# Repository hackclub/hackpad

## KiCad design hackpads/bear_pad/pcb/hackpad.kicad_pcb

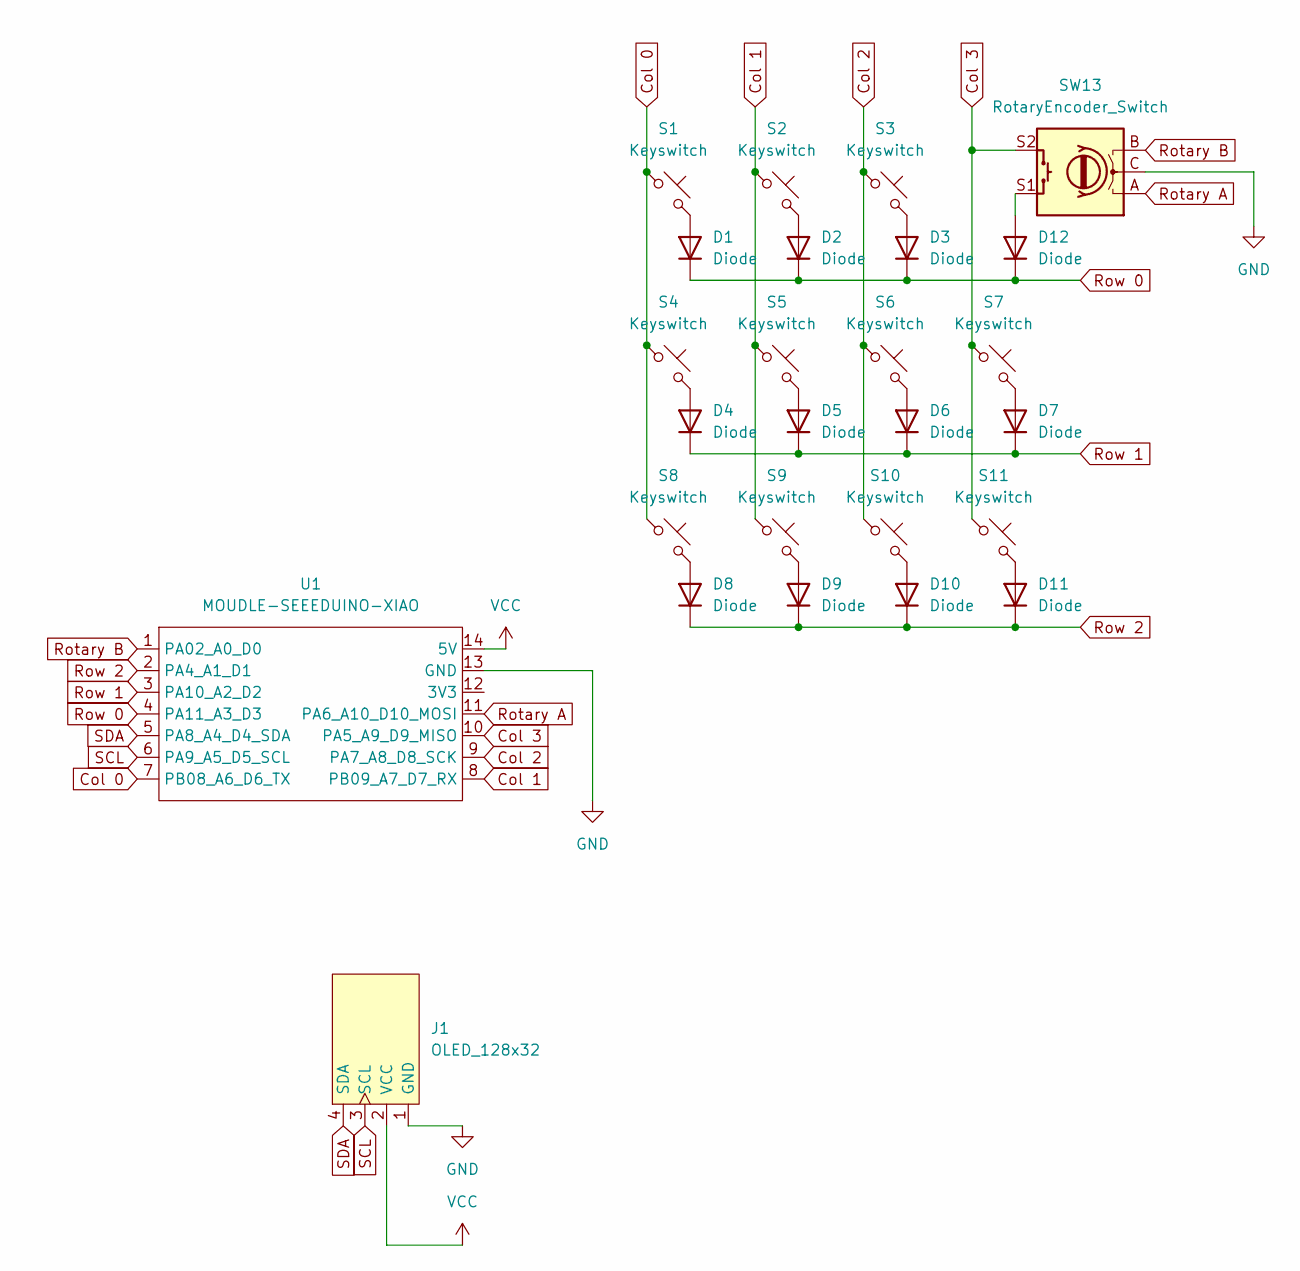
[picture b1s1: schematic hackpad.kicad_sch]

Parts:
D1, D2, D3, D4, D5, D6, D7, D8, D9, D10, D11, D12: Diode; Diode_DO-35
J1: OLED_128x32
S1, S2, S3, S4, S5, S6, S7, S8, S9, S10, S11: Keyswitch; MX_PCB_1.00u
SW13: RotaryEncoder_Switch; RotaryEncoder_Alps_EC11E-Switch_Vertical_H20mm
U1: MOUDLE-SEEEDUINO-XIAO; XIAO-Generic-Hybrid-14P-2.54-21X17.8MM

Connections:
Col 0: S1.1, S4.1, S8.1, U1.7 (PB08_A6_D6_TX)
Col 1: S2.1, S5.1, S9.1, U1.8 (PB09_A7_D7_RX)
Col 2: S3.1, S6.1, S10.1, U1.9 (PA7_A8_D8_SCK)
Col 3: S7.1, S11.1, SW13.S2, U1.10 (PA5_A9_D9_MISO)
GND: J1.1 (GND), SW13.C, U1.13 (GND)
unnamed: D1.2 (A), S1.2
unnamed: D2.2 (A), S2.2
unnamed: D3.2 (A), S3.2
unnamed: D4.2 (A), S4.2
unnamed: D5.2 (A), S5.2
unnamed: D6.2 (A), S6.2
unnamed: D7.2 (A), S7.2
unnamed: D8.2 (A), S8.2
unnamed: D9.2 (A), S9.2
unnamed: D10.2 (A), S10.2
unnamed: D11.2 (A), S11.2
unnamed: D12.2 (A), SW13.S1
Rotary A: SW13.A, U1.11 (PA6_A10_D10_MOSI)
Rotary B: SW13.B, U1.1 (PA02_A0_D0)
Row 0: D1.1 (K), D2.1 (K), D3.1 (K), D12.1 (K), U1.4 (PA11_A3_D3)
Row 1: D4.1 (K), D5.1 (K), D6.1 (K), D7.1 (K), U1.3 (PA10_A2_D2)
Row 2: D8.1 (K), D9.1 (K), D10.1 (K), D11.1 (K), U1.2 (PA4_A1_D1)
SCL: J1.3 (SCL), U1.6 (PA9_A5_D5_SCL)
SDA: J1.4 (SDA), U1.5 (PA8_A4_D4_SDA)
VCC: J1.2 (VCC), U1.14 (5V)

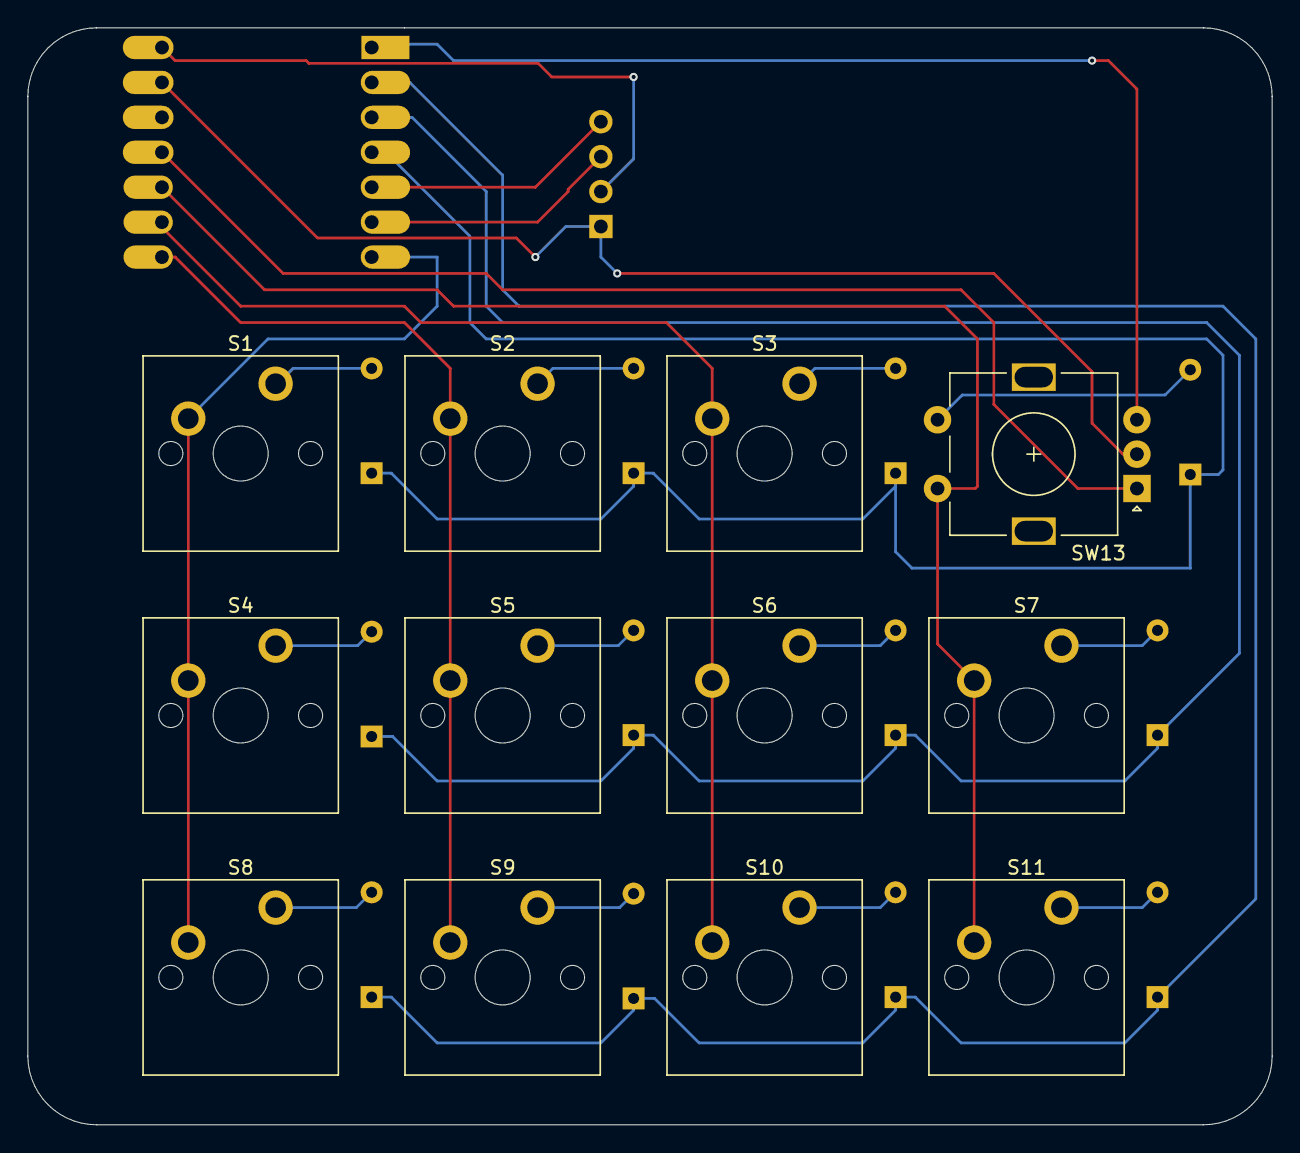
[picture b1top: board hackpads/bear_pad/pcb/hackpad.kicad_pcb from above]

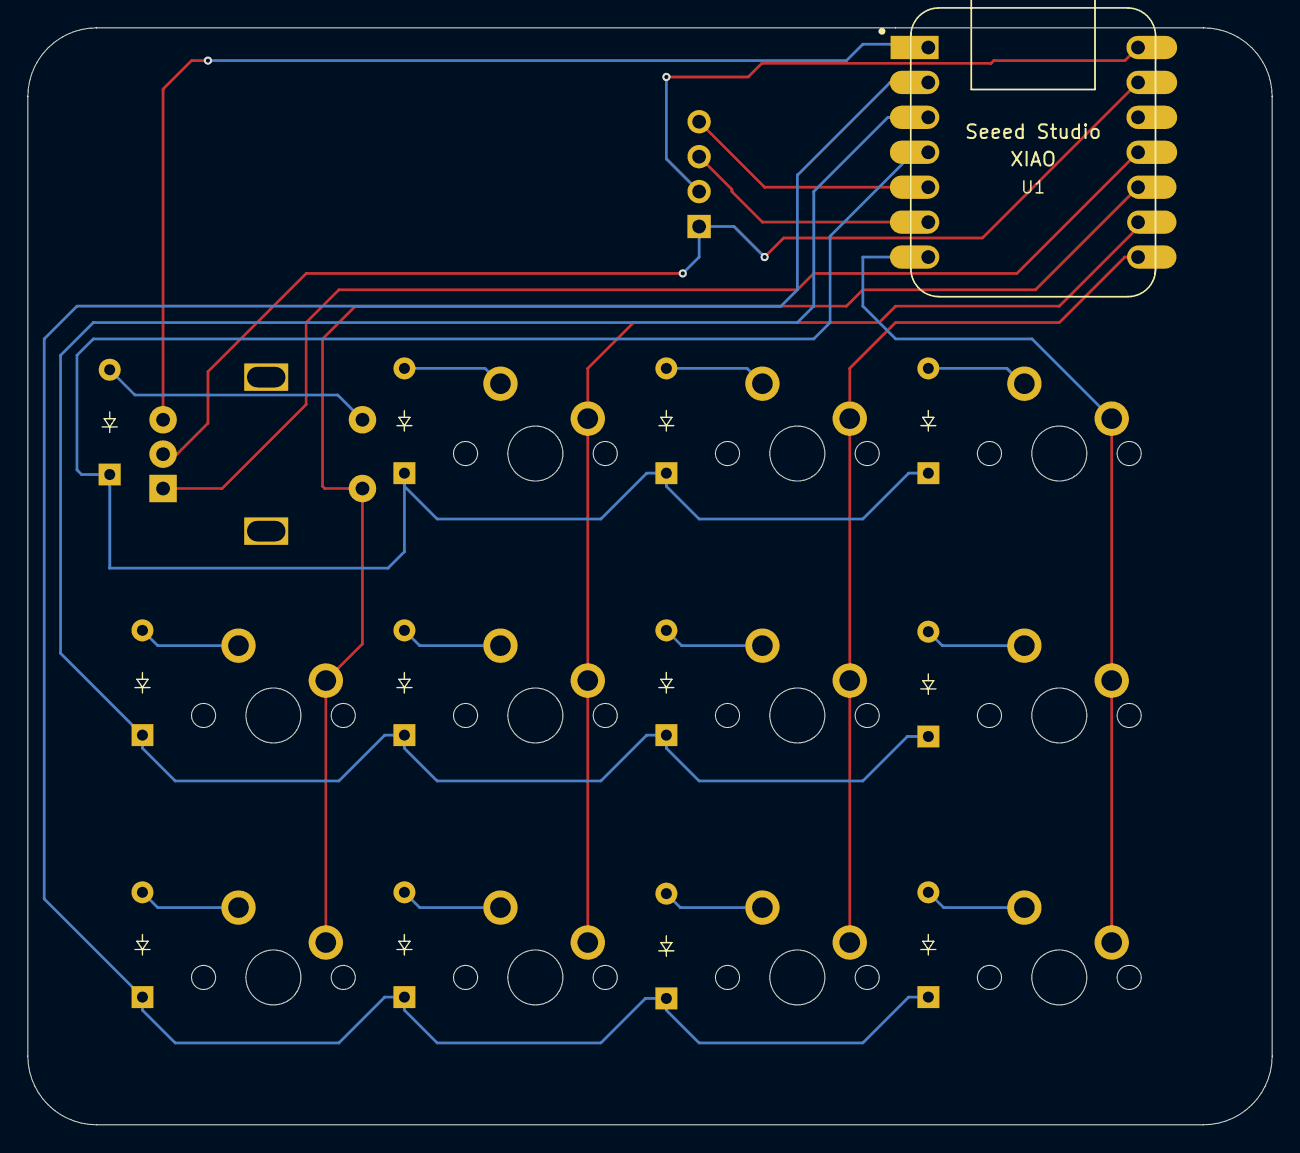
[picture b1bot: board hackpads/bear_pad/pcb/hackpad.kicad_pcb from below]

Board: 2 copper layers, 90.5 x 79.8 mm, 26 parts (13 on the bottom side), 25 nets.

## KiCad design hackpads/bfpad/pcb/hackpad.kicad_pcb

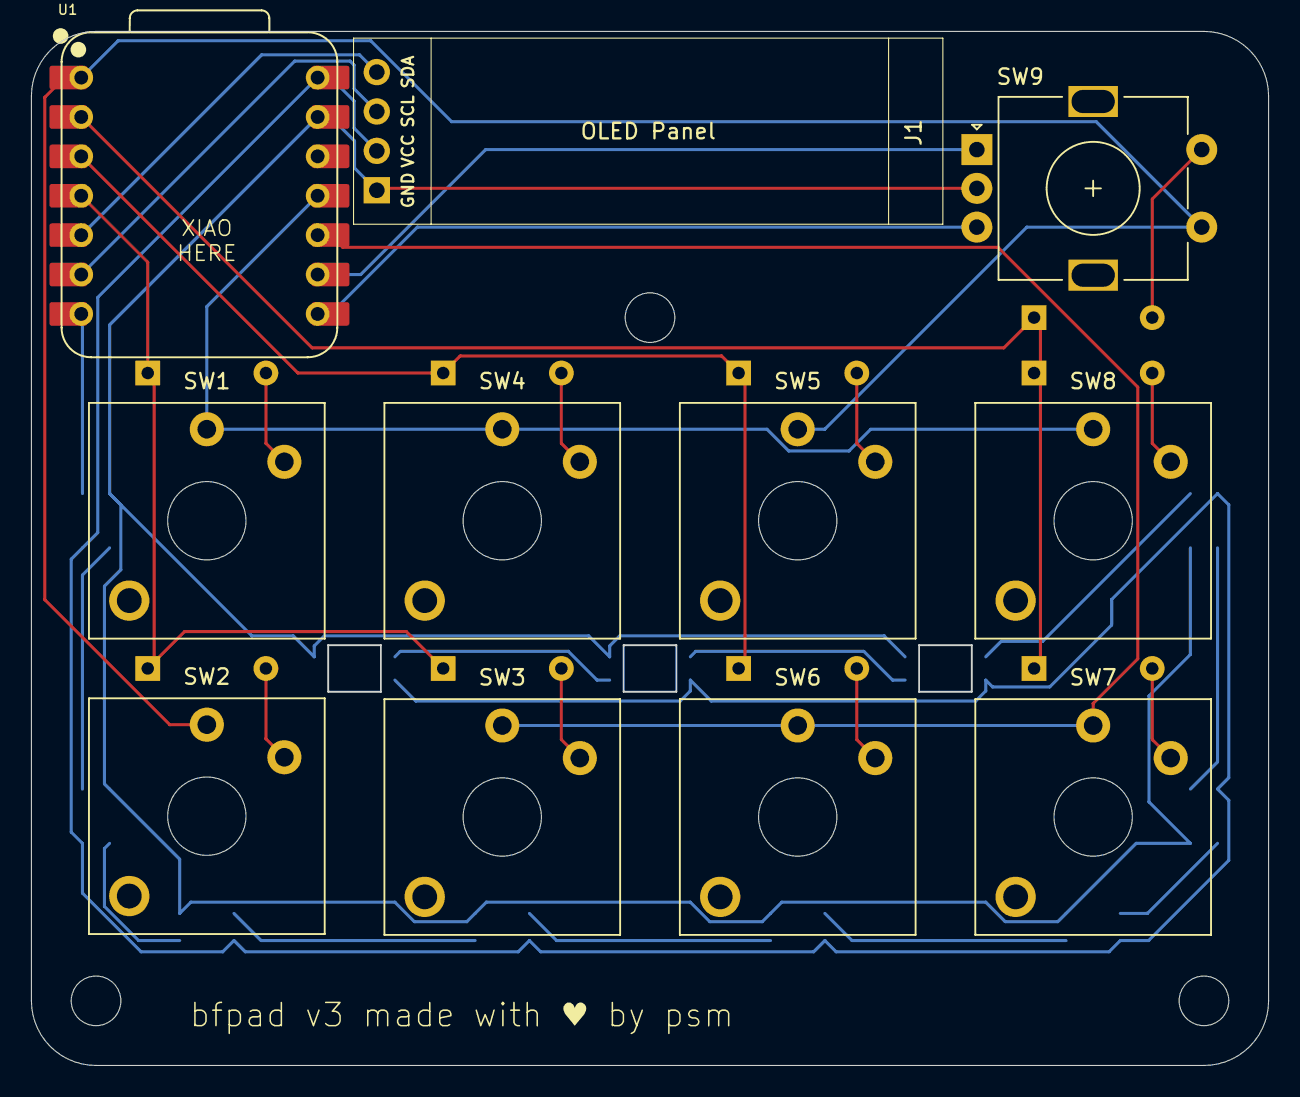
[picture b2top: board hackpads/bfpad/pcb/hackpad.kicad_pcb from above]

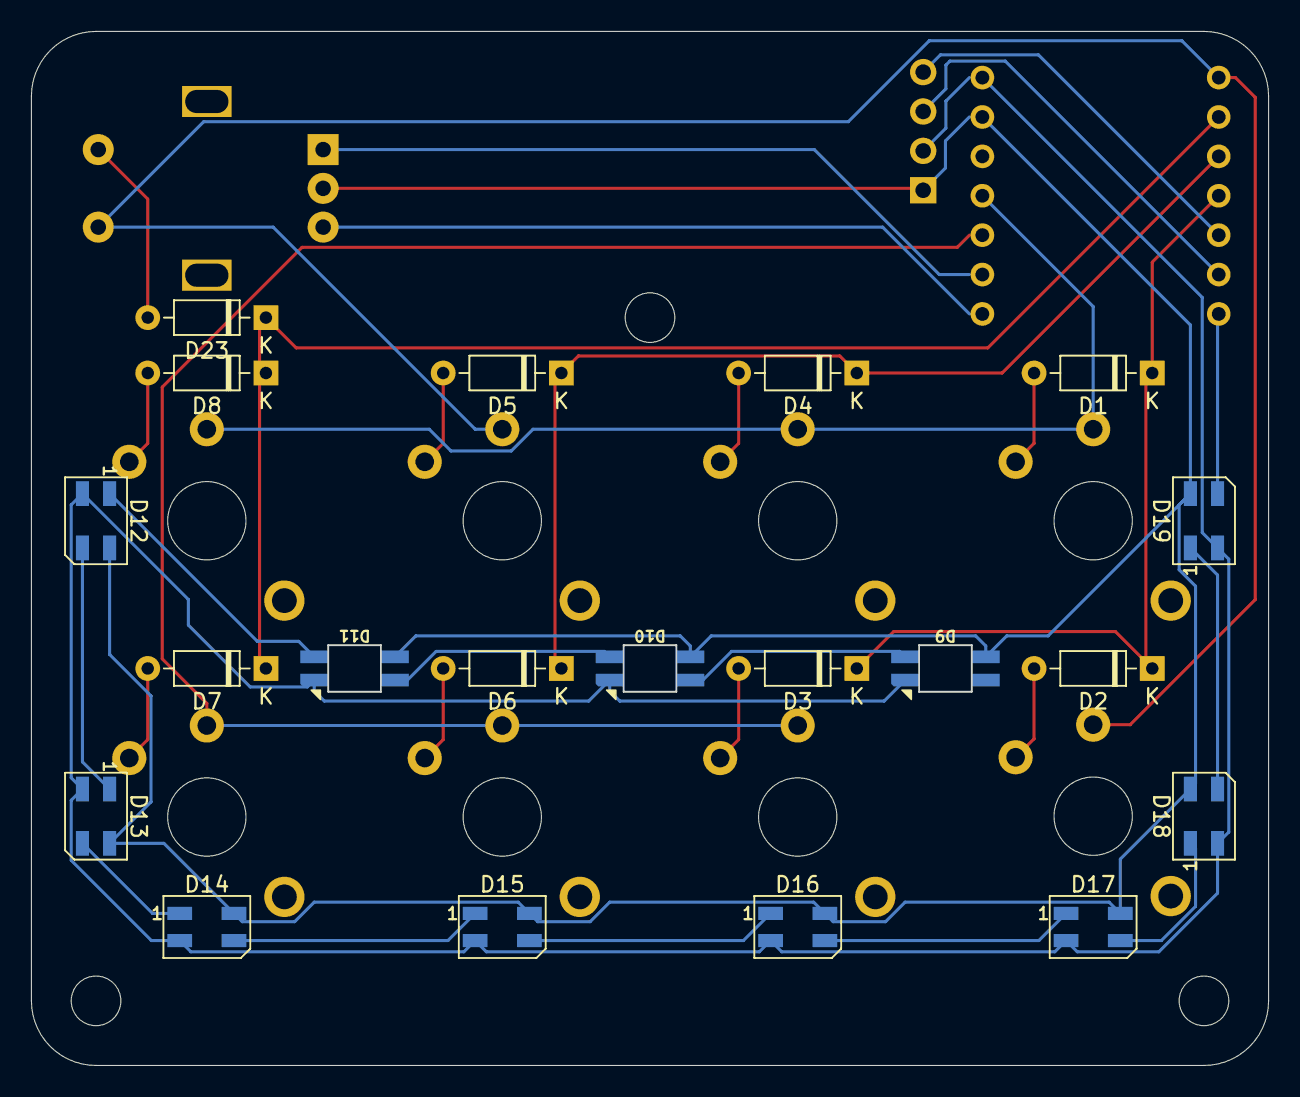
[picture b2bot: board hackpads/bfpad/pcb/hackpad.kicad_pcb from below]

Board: 2 copper layers, 79.8 x 66.7 mm, 31 parts (20 on the bottom side), 32 nets.

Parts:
D1, D2, D3, D4, D5, D6, D7, D8, D23: D; D_DO-35_SOD27_P7.62mm_Horizontal
D9, D10, D11: SK6812MINI; SK6812MINI-E
D12, D13, D14, D15, D16, D17, D18, D19: SK6812MINI; LED_SK6812MINI_PLCC4_3.5x3.5mm_P1.75mm
J1: SSD1306; SSD1306-0.91-OLED-4pin-128x32
SW1, SW2, SW3, SW4, SW5, SW6, SW7, SW8: SW_Push; SW_Kailh_Choc_V2
SW9: RotaryEncoder_Switch; RotaryEncoder_Alps_EC11E-Switch_Vertical_H20mm
U1: XIAO-RP2040-DIP

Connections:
+5V: D9.2 (VSS), D10.2 (VSS), D11.2 (VSS), D12.2 (VSS), D13.2 (VSS), D14.2 (VSS), D15.2 (VSS), D16.2 (VSS), D17.2 (VSS), D18.2 (VSS), D19.2 (VSS), J1.2, U1.14 (VBUS)
COL1: SW1.1, SW4.1, SW8.1, U1.11 (GPIO3/MOSI)
COL2: SW2.1, SW5.1, SW9.S1, U1.1 (GPIO26/ADC0/A0)
COL3: SW3.1, SW6.1, SW7.1, U1.10 (GPIO4/MISO)
GND: D9.4 (VDD), D10.4 (VDD), D11.4 (VDD), D12.4 (VDD), D13.4 (VDD), D14.4 (VDD), D15.4 (VDD), D16.4 (VDD), D17.4 (VDD), D18.4 (VDD), D19.4 (VDD), J1.1, SW9.C, U1.13 (GND)
unnamed: D1.2 (A), SW1.2
unnamed: D2.2 (A), SW2.2
unnamed: D3.2 (A), SW3.2
unnamed: D4.2 (A), SW4.2
unnamed: D5.2 (A), SW5.2
unnamed: D6.2 (A), SW6.2
unnamed: D7.2 (A), SW7.2
unnamed: D8.2 (A), SW8.2
unnamed: D10.3 (DIN), D11.1 (DOUT)
unnamed: D9.3 (DIN), D10.1 (DOUT)
unnamed: D11.3 (DIN), D12.1 (DOUT)
unnamed: D12.3 (DIN), D13.1 (DOUT)
unnamed: D13.3 (DIN), D14.1 (DOUT)
unnamed: D14.3 (DIN), D15.1 (DOUT)
unnamed: D15.3 (DIN), D16.1 (DOUT)
unnamed: D16.3 (DIN), D17.1 (DOUT)
unnamed: D17.3 (DIN), D18.1 (DOUT)
unnamed: D18.3 (DIN), D19.1 (DOUT)
unnamed: D19.3 (DIN), U1.7 (GPIO0/TX)
REA: SW9.A, U1.9 (GPIO2/SCK)
REB: SW9.B, U1.8 (GPIO1/RX)
RES2: D23.2 (A), SW9.S2
ROW1: D1.1 (K), D2.1 (K), D3.1 (K), U1.4 (GPIO29/ADC3/A3)
ROW2: D4.1 (K), D5.1 (K), D6.1 (K), U1.3 (GPIO28/ADC2/A2)
ROW3: D7.1 (K), D8.1 (K), D23.1 (K), U1.2 (GPIO27/ADC1/A1)
SCL: J1.3, U1.6 (GPIO7/SCL)
SDA: J1.4, U1.5 (GPIO6/SDA)

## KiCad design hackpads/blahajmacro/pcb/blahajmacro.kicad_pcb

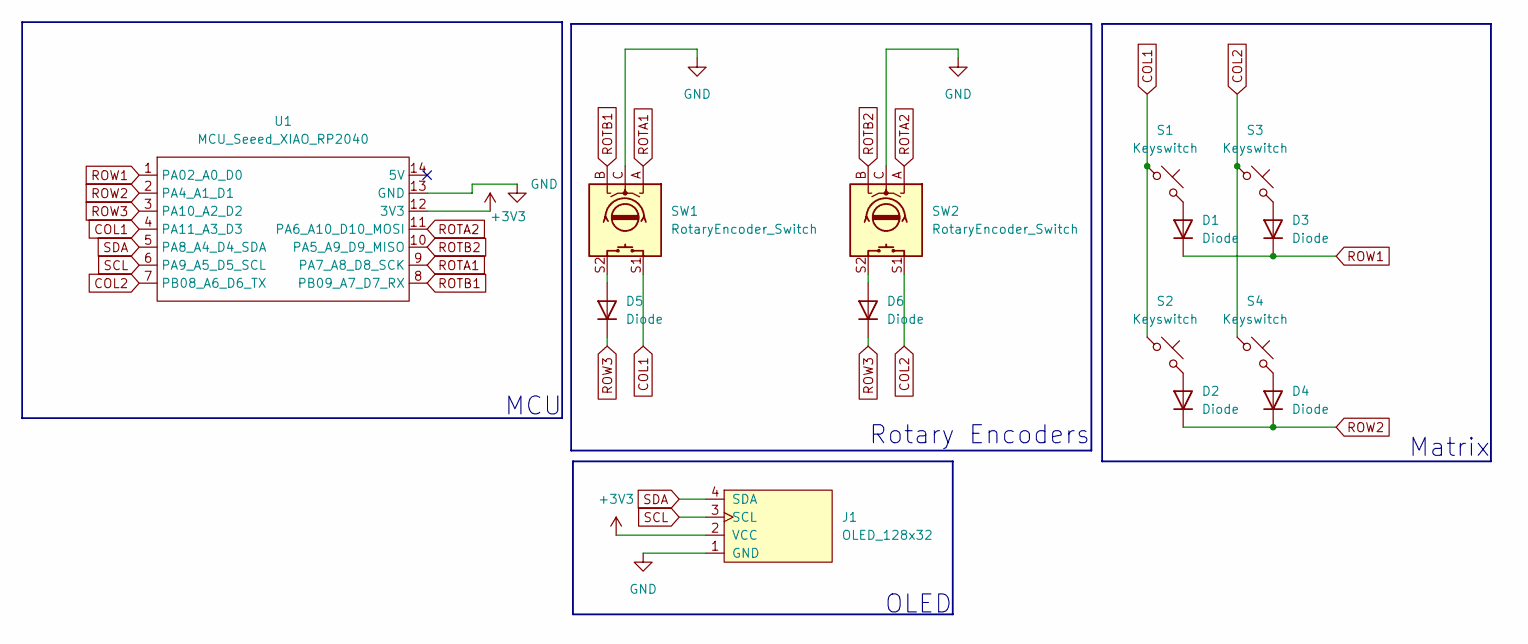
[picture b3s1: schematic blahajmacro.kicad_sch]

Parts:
D1, D2, D3, D4, D5, D6: Diode; Diode_DO-35
J1: OLED_128x32
S1, S2, S3, S4: Keyswitch; MX_Hotswap_1.00u
SW1, SW2: RotaryEncoder_Switch; Encoder_EC11_MX
U1: MCU_Seeed_XIAO_RP2040; Seeed_XIAO_RP2040

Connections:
+3V3: J1.2 (VCC), U1.12 (3V3)
COL1: S1.1, S2.1, SW1.S1, U1.4 (PA11_A3_D3)
COL2: S3.1, S4.1, SW2.S1, U1.7 (PB08_A6_D6_TX)
GND: J1.1 (GND), SW1.C, SW2.C, U1.13 (GND)
unnamed: D1.2 (A), S1.2
unnamed: D2.2 (A), S2.2
unnamed: D3.2 (A), S3.2
unnamed: D4.2 (A), S4.2
unnamed: D5.2 (A), SW1.S2
unnamed: D6.2 (A), SW2.S2
ROTA1: SW1.A, U1.9 (PA7_A8_D8_SCK)
ROTA2: SW2.A, U1.11 (PA6_A10_D10_MOSI)
ROTB1: SW1.B, U1.8 (PB09_A7_D7_RX)
ROTB2: SW2.B, U1.10 (PA5_A9_D9_MISO)
ROW1: D1.1 (K), D3.1 (K), U1.1 (PA02_A0_D0)
ROW2: D2.1 (K), D4.1 (K), U1.2 (PA4_A1_D1)
ROW3: D5.1 (K), D6.1 (K), U1.3 (PA10_A2_D2)
SCL: J1.3 (SCL), U1.6 (PA9_A5_D5_SCL)
SDA: J1.4 (SDA), U1.5 (PA8_A4_D4_SDA)

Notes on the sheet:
MCU
Rotary Encoders
Matrix
OLED

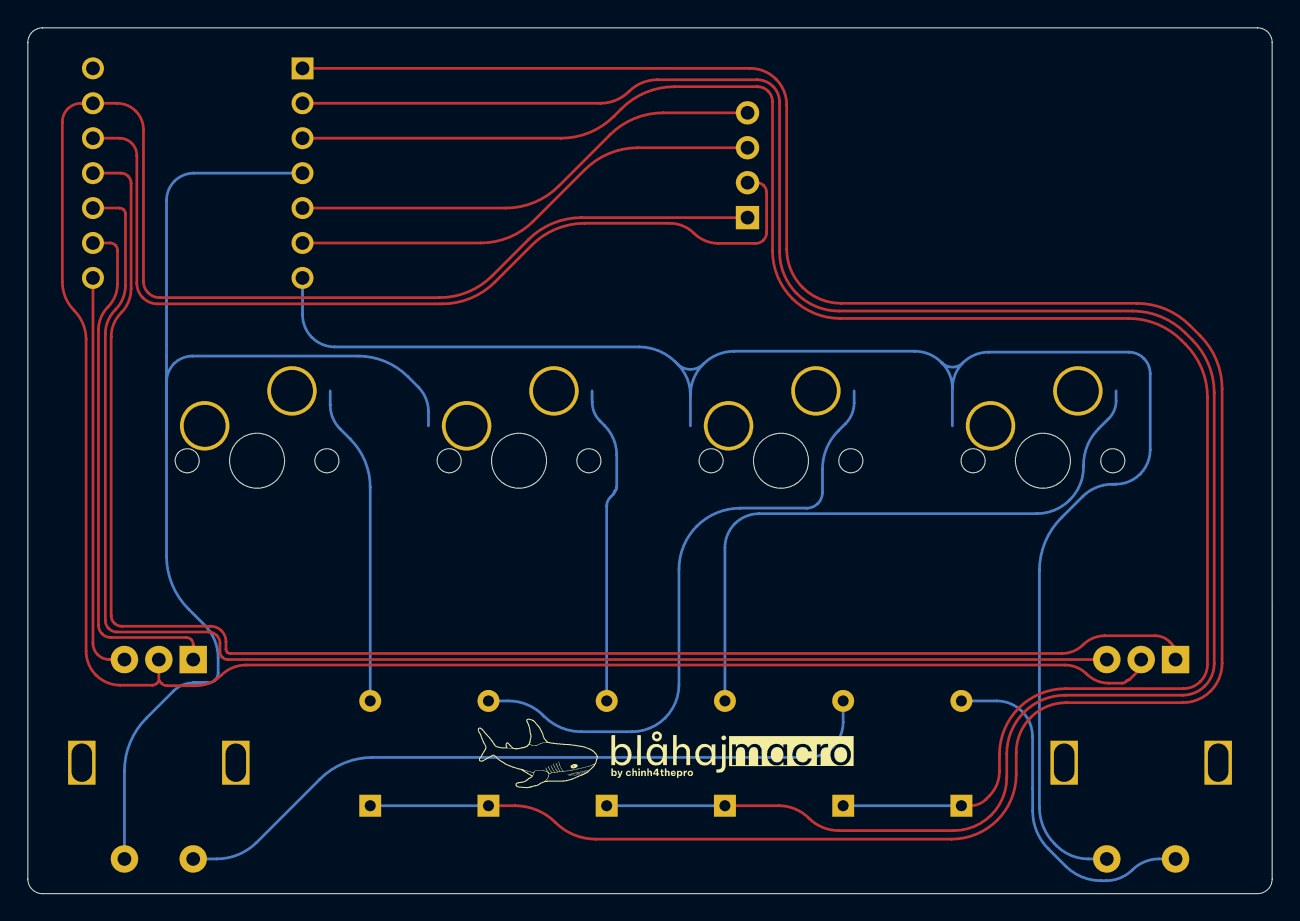
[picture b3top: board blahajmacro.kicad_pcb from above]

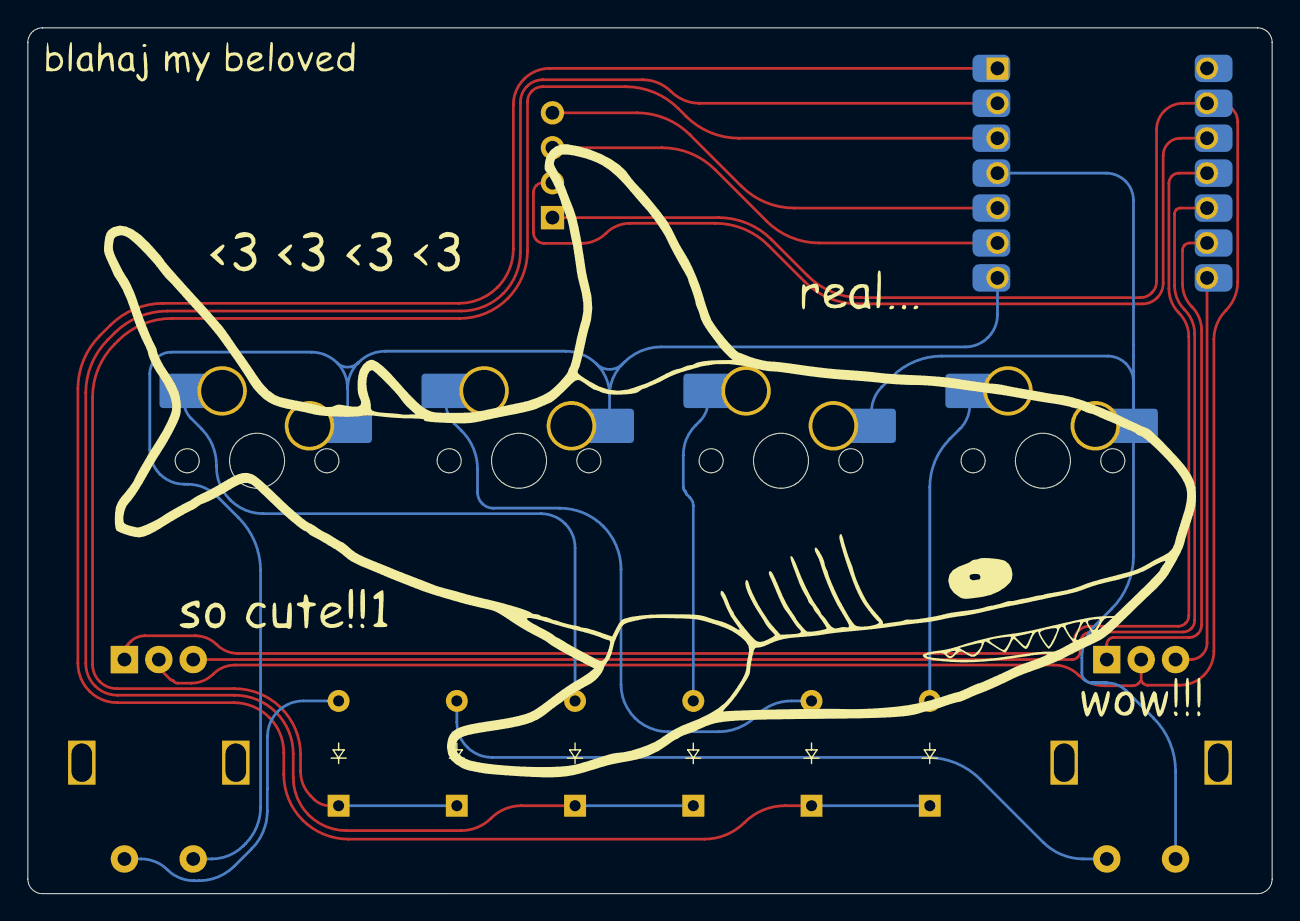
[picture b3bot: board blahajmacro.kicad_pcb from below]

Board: 2 copper layers, 90.5 x 63.0 mm, 14 parts (11 on the bottom side), 19 nets.

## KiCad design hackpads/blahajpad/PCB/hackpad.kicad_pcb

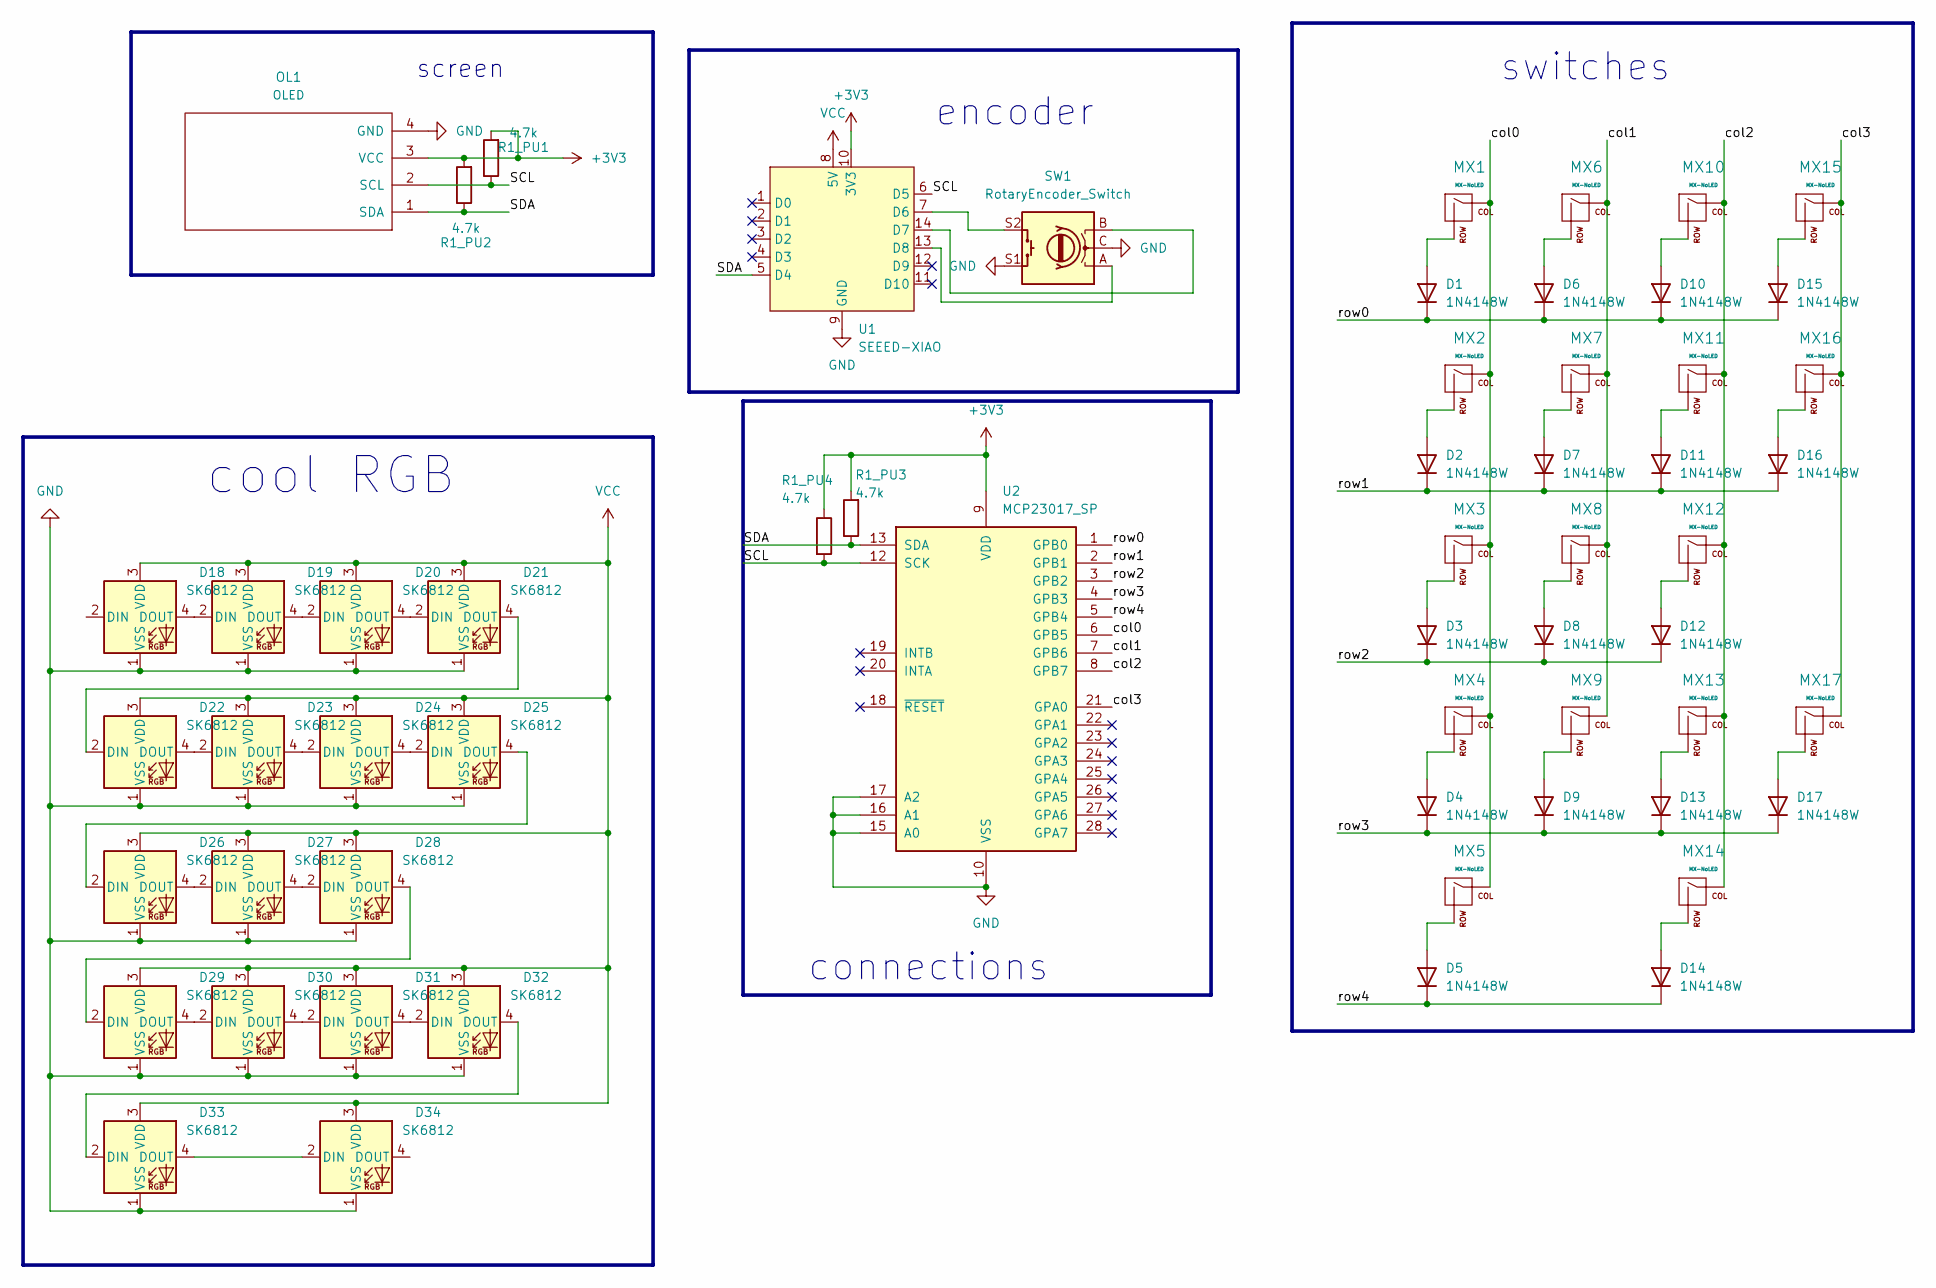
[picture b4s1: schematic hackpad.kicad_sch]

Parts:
D1, D2, D3, D4, D5, D6, D7, D8, D9, D10, D11, D12, D13, D14, D15, D16, D17: 1N4148W; D_DO-35_SOD27_P7.62mm_Horizontal
D18, D19, D20, D21, D22, D23, D24, D25, D26, D27, D28, D29, D30, D31, D32, D33, D34: SK6812; SK6812MINI-E
MX1, MX2, MX3, MX4, MX6, MX7, MX8, MX9, MX10, MX11, MX12, MX13, MX14, MX15: MX-NoLED; MX-Solderable-1U
MX5: MX-NoLED; MX-Solderable-2U
MX16, MX17: MX-NoLED; MX-Solderable-2U-Vertical
OL1: OLED; SSD1306-0.91-OLED-4pin-128x32
R1_PU1, R1_PU2, R1_PU3, R1_PU4: 4.7k; R_Axial_DIN0204_L3.6mm_D1.6mm_P7.62mm_Horizontal
SW1: RotaryEncoder_Switch; RotaryEncoder_Alps_EC11E-Switch_Vertical_H20mm
U1: SEEED-XIAO; XIAO-14P-SMD-2.54-21x17.8MM
U2: MCP23017_SP; DIP-28_W7.62mm

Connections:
+3V3: OL1.3 (VCC), R1_PU1.2, R1_PU2.2, R1_PU3.2, R1_PU4.1, U1.10 (3V3), U2.9 (VDD)
/SCL: OL1.2 (SCL), R1_PU1.1, R1_PU4.2, U1.6 (D5), U2.12 (SCK)
/SDA: OL1.1 (SDA), R1_PU2.1, R1_PU3.1, U1.5 (D4), U2.13 (SDA)
/col0: MX1.1 (COL), MX2.1 (COL), MX3.1 (COL), MX4.1 (COL), MX5.1 (COL), U2.6 (GPB5)
/col1: MX6.1 (COL), MX7.1 (COL), MX8.1 (COL), MX9.1 (COL), U2.7 (GPB6)
/col2: MX10.1 (COL), MX11.1 (COL), MX12.1 (COL), MX13.1 (COL), MX14.1 (COL), U2.8 (GPB7)
/col3: MX15.1 (COL), MX16.1 (COL), MX17.1 (COL), U2.21 (GPA0)
/row0: D1.1 (K), D6.1 (K), D10.1 (K), D15.1 (K), U2.1 (GPB0)
/row1: D2.1 (K), D7.1 (K), D11.1 (K), D16.1 (K), U2.2 (GPB1)
/row2: D3.1 (K), D8.1 (K), D12.1 (K), U2.3 (GPB2)
/row3: D4.1 (K), D9.1 (K), D13.1 (K), D17.1 (K), U2.4 (GPB3)
/row4: D5.1 (K), D14.1 (K), U2.5 (GPB4)
GND: D18.1 (VSS), D19.1 (VSS), D20.1 (VSS), D21.1 (VSS), D22.1 (VSS), D23.1 (VSS), D24.1 (VSS), D25.1 (VSS), D26.1 (VSS), D27.1 (VSS), D28.1 (VSS), D29.1 (VSS), D30.1 (VSS), D31.1 (VSS), D32.1 (VSS), D33.1 (VSS), D34.1 (VSS), OL1.4 (GND), SW1.C, SW1.S1, U1.9 (GND), U2.10 (VSS), U2.15 (A0), U2.16 (A1), U2.17 (A2)
unnamed: D1.2 (A), MX1.2 (ROW)
unnamed: D2.2 (A), MX2.2 (ROW)
unnamed: D3.2 (A), MX3.2 (ROW)
unnamed: D4.2 (A), MX4.2 (ROW)
unnamed: D5.2 (A), MX5.2 (ROW)
unnamed: D6.2 (A), MX6.2 (ROW)
unnamed: D7.2 (A), MX7.2 (ROW)
unnamed: D8.2 (A), MX8.2 (ROW)
unnamed: D9.2 (A), MX9.2 (ROW)
unnamed: D10.2 (A), MX10.2 (ROW)
unnamed: D11.2 (A), MX11.2 (ROW)
unnamed: D12.2 (A), MX12.2 (ROW)
unnamed: D13.2 (A), MX13.2 (ROW)
unnamed: D14.2 (A), MX14.2 (ROW)
unnamed: D15.2 (A), MX15.2 (ROW)
unnamed: D16.2 (A), MX16.2 (ROW)
unnamed: D17.2 (A), MX17.2 (ROW)
unnamed: D18.4 (DOUT), D19.2 (DIN)
unnamed: D19.4 (DOUT), D20.2 (DIN)
unnamed: D20.4 (DOUT), D21.2 (DIN)
unnamed: D21.4 (DOUT), D22.2 (DIN)
unnamed: D22.4 (DOUT), D23.2 (DIN)
unnamed: D23.4 (DOUT), D24.2 (DIN)
unnamed: D24.4 (DOUT), D25.2 (DIN)
unnamed: D25.4 (DOUT), D26.2 (DIN)
unnamed: D26.4 (DOUT), D27.2 (DIN)
unnamed: D27.4 (DOUT), D28.2 (DIN)
unnamed: D28.4 (DOUT), D29.2 (DIN)
unnamed: D29.4 (DOUT), D30.2 (DIN)
unnamed: D30.4 (DOUT), D31.2 (DIN)
unnamed: D31.4 (DOUT), D32.2 (DIN)
unnamed: D32.4 (DOUT), D33.2 (DIN)
unnamed: D33.4 (DOUT), D34.2 (DIN)
unnamed: SW1.S2, U1.7 (D6)
unnamed: SW1.B, U1.14 (D7)
unnamed: SW1.A, U1.13 (D8)
VCC: D18.3 (VDD), D19.3 (VDD), D20.3 (VDD), D21.3 (VDD), D22.3 (VDD), D23.3 (VDD), D24.3 (VDD), D25.3 (VDD), D26.3 (VDD), D27.3 (VDD), D28.3 (VDD), D29.3 (VDD), D30.3 (VDD), D31.3 (VDD), D32.3 (VDD), D33.3 (VDD), D34.3 (VDD), U1.8 (5V)

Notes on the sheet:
connections
encoder
screen
switches
cool RGB

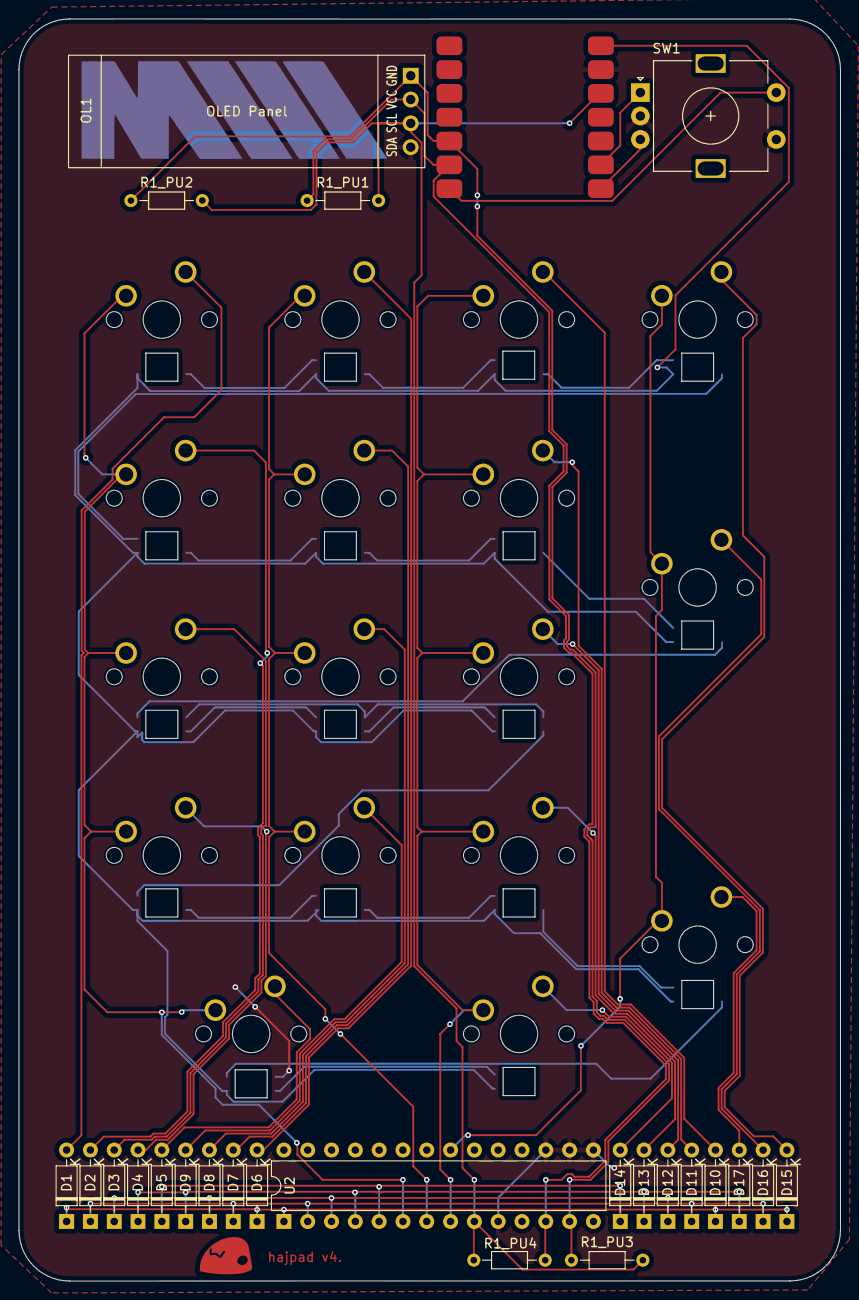
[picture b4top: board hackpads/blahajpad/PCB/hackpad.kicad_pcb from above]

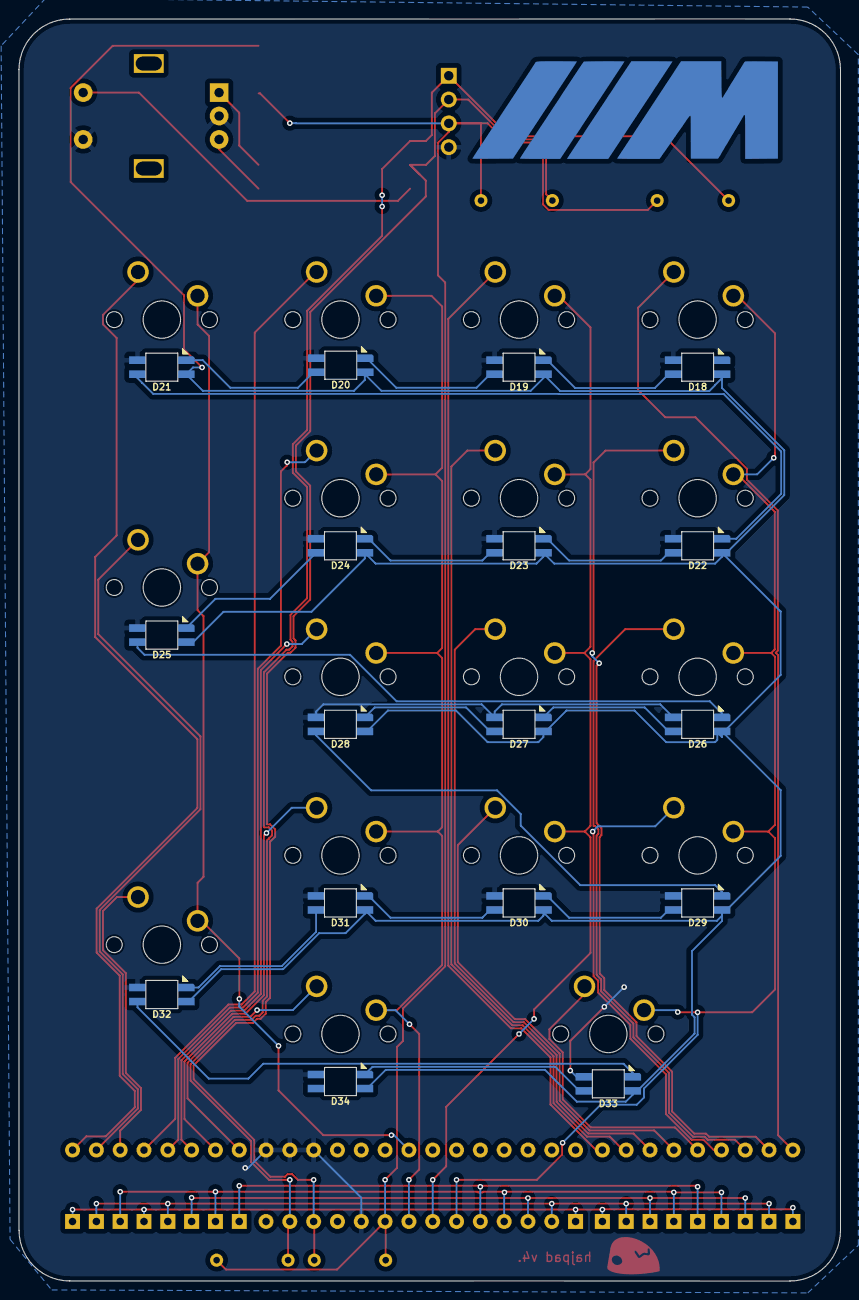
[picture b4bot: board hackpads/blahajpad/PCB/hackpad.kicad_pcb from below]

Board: 2 copper layers, 87.6 x 134.6 mm, 61 parts (19 on the bottom side), 50 nets.

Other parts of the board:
., .#2: .; LOGO

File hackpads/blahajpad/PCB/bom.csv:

Designator,Footprint,Quantity,Value,LCSC Part #
"D1, D10, D11, D12, D13, D14, D15, D16, D17, D2, D3, D4, D5, D6, D7, D8, D9",D_DO-35_SOD27_P7.62mm_Horizontal,17,1N4148W,
"D18, D19, D20, D21, D22, D23, D24, D25, D26, D27, D28, D29, D30, D31, D32, D33, D34",SK6812MINI-E,17,SK6812,
"MX1, MX10, MX11, MX12, MX13, MX14, MX15, MX2, MX3, MX4, MX6, MX7, MX8, MX9",MX-Solderable-1U,14,MX-NoLED,
"MX16, MX17",MX-Solderable-2U-Vertical,2,MX-NoLED,
MX5,MX-Solderable-2U,1,MX-NoLED,
OL1,SSD1306-0.91-OLED-4pin-128x32,1,OLED,
"R1_PU1, R1_PU2, R1_PU3, R1_PU4",R_Axial_DIN0204_L3.6mm_D1.6mm_P7.62mm_Horizontal,4,4.7k,
SW1,RotaryEncoder_Alps_EC11E-Switch_Vertical_H20mm,1,RotaryEncoder_Switch,
U1,XIAO-14P-SMD-2.54-21x17.8MM,1,SEEED-XIAO,
U2,DIP-28_W7.62mm,1,MCP23017_SP,
